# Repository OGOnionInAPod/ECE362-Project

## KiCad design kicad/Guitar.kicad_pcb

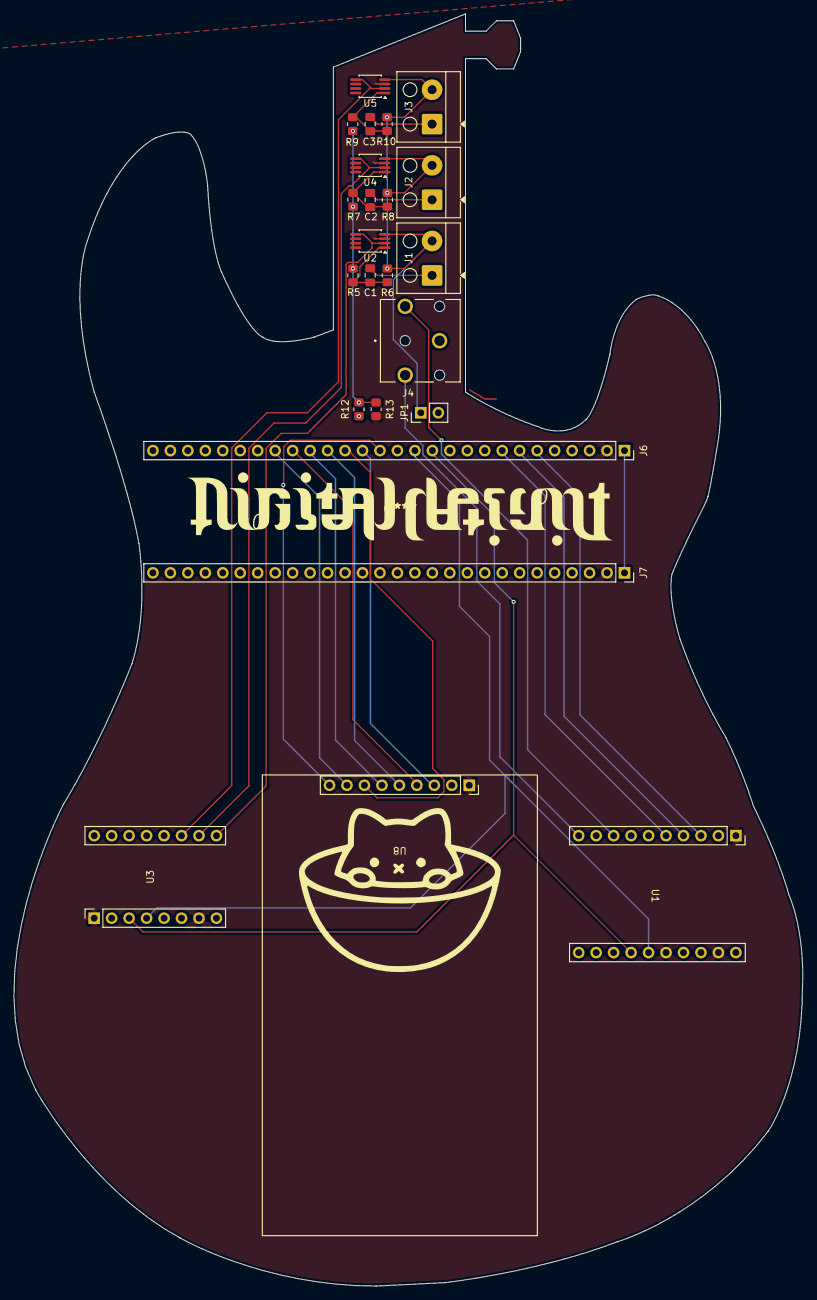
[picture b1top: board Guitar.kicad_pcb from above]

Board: 2 copper layers, 114.7 x 185.0 mm, 24 parts (0 on the bottom side), 28 nets.

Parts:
C1, C2, C3: 1uF; C_0805_2012Metric_Pad1.18x1.45mm_HandSolder
J1: Pickup1; Altech_AK100_1x02_P5.00mm
J2: Pickup2; Altech_AK100_1x02_P5.00mm
J3: Pickup3; Altech_AK100_1x02_P5.00mm
J4: SJ1-3543N; CUI_SJ1-3543N
J6, J7: Conn_01x28_Pin; PinSocket_1x28_P2.54mm_Vertical
JP1: Jumper_2_Open; PinHeader_1x02_P2.54mm_Vertical
R5, R7, R9: 1k; R_0805_2012Metric_Pad1.20x1.40mm_HandSolder
R6, R8, R10, R12, R13: 1M; R_0805_2012Metric_Pad1.20x1.40mm_HandSolder
U1: dac
U2, U4, U5: MSOP-8_3x3mm_P0.65mm
U3: adc
U8: oled

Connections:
+1.65V: R5.1, R7.1, R9.1, R12.1, R13.2
+3V3: J6.2, J7.2, R13.1, U1.1 (vin), U1.16 (mod2), U1.19 (a2), U2.3 (V+), U3.1 (Vin), U3.7 (avdd), U4.3 (V+), U5.3 (V+), U8.1 (vcc)
/AnalogFrontend/CH1_OUT: U2.2 (-), U2.5, U3.9 (a0)
/AnalogFrontend/CH2_OUT: U3.10 (a1), U4.2 (-), U4.5
/AnalogFrontend/CH3_OUT: U3.11 (a2), U5.2 (-), U5.5
/AnalogFrontend/P1_IN: C1.1, J1.1
/AnalogFrontend/P2_IN: C2.1, J2.1
/AnalogFrontend/P3_IN: C3.1, J3.1
/GPIO3: J6.6, U1.3 (wsel)
/GPIO4: J6.7, U1.4 (din)
/GPIO5: J6.8, U1.5 (bck)
/GPIO9: J6.12, U1.14 (scl), U3.3 (scl)
/GPIO10: J6.13, U1.15 (sda), U3.4 (sda)
/GPIO12: J6.15, U8.9 (sdo/miso)
/GPIO13: J6.16, U8.3 (cs)
/GPIO14: J6.17, U8.7 (sck)
/GPIO15: J6.18, U8.5 (dc/rs)
/GPIO16: J6.19, U8.6 (sdi/mosi)
/GPIO17: J6.20, U8.4 (rst)
/GPIO18: J6.21, U8.8 (led)
GND: J4.1, J6.28, J7.28, JP1.2 (B), R12.2, U1.2 (gnd), U1.9 (gnd), U1.17 (mod1), U1.18 (agin), U1.20 (a1/fmt), U3.2 (gnd), U3.5 (addr), U3.8 (gnd), U8.2 (gnd)
GNDA: J1.2, J2.2, J3.2, JP1.1 (A), R6.2, R8.2, R10.2, U2.4 (V-), U4.4 (V-), U5.4 (V-)
unnamed: J4.2, U1.8 (Lout)
unnamed: J4.3, U1.10 (rout)
unnamed: C1.2, R5.2, R6.1, U2.1 (+)
unnamed: C2.2, R7.2, R8.1, U4.1 (+)
unnamed: C3.2, R9.2, R10.1, U5.1 (+)
VBUS: J6.1, J7.1
